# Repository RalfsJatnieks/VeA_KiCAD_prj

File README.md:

# VeA_KiCAD_prj
i bus reprezotorija maniem kursa darbiem

Link uz mikroshemu https://www.onsemi.com/pub/Collateral/BC847BPDXV6T1-D.PDF

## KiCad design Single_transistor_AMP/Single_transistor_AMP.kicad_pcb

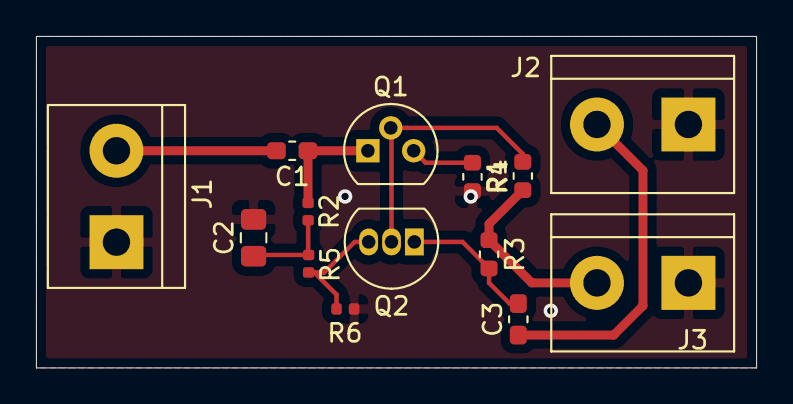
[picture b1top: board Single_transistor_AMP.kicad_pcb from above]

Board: 2 copper layers, 40.0 x 18.4 mm, 14 parts (0 on the bottom side), 9 nets.

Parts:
C1, C3: 22uF; C_0603_1608Metric_Pad1.05x0.95mm_HandSolder
C2: 47uF; C_0805_2012Metric_Pad1.15x1.40mm_HandSolder
J1: Signals ieeja; TerminalBlock_bornier-2_P5.08mm
J2: Signals izeja; TerminalBlock_bornier-2_P5.08mm
J3: 12V; TerminalBlock_bornier-2_P5.08mm
Q1: BC548; TO-92
Q2: BC548; TO-92_Inline
R1: 22K; R_0603_1608Metric
R2: 6,8K; R_0402_1005Metric
R3: 47K; R_0603_1608Metric
R4: 1,8K; R_0603_1608Metric
R5, R6: 1K; R_0402_1005Metric

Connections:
GND: C2.2, J1.1, J2.1, J3.1, R4.2, R6.2
unnamed: C1.1, C1.2, J1.2, Q1.1, R2.1
unnamed: C2.1, R2.2, R5.2
unnamed: C3.1, J2.2
unnamed: C3.2, Q2.1, R3.2
unnamed: J3.2, R1.1, R3.1
unnamed: Q1.2, Q2.2, R1.2
unnamed: Q1.3, R4.1
unnamed: Q2.3, R5.1, R6.1

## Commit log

2020-10-01 Pirmais edit
2020-10-07 majasdarbs
2020-10-08 mikroshemas link
2020-10-08 dzesu failu
2020-10-12 Otrais MD
2020-10-27 4mdOtraDalja
2020-12-11 Add files via upload
    Bom atskaite, SVG attēli
